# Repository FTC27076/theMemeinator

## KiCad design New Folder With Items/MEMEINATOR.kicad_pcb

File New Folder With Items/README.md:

# theMemeinator

This is my week 3 project. 
This week I designed something kinda like week 1; it's a speaker thingy that reads recording files and plays them.

# Components I used:

4xAA battery holder

USB_C PORT

Potentiometer (for volume)

five push switches (1 for reseting, 1 for ____, 3 for cataloging and choosing )

1 slide switch for power

ESP32 S3 Wroom-1

DFPlayer mini

MCP1825s

# Passive components:

Resistors

capacitors 

Schotty diode

two 2 pin JST PH connector

## FINAL PRODUCT:

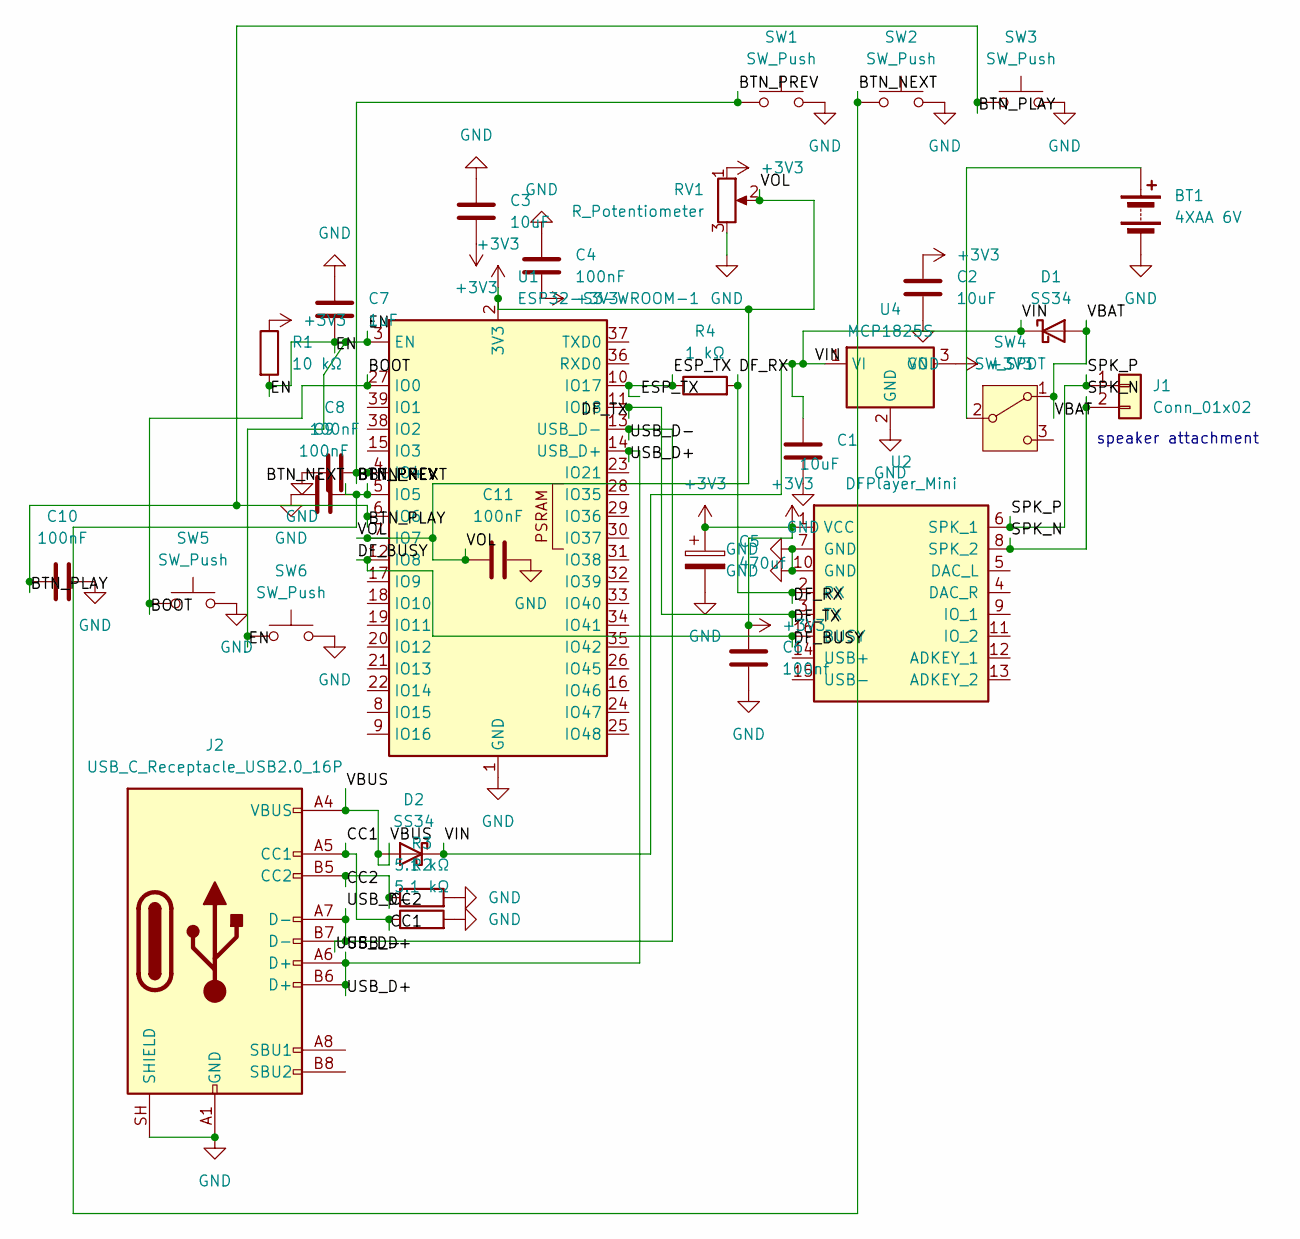
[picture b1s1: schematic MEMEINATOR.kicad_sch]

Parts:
BT1: 4XAA 6V; JST_PH_B2B-PH-K_1x02_P2.00mm_Vertical
C1, C2, C3: 10uF; C_Disc_D3.0mm_W1.6mm_P2.50mm
C4, C8, C9, C10, C11: 100nF; C_Disc_D3.0mm_W1.6mm_P2.50mm
C5: 470uf; CP_Radial_D8.0mm_P3.50mm
C6: 100nf; C_Disc_D3.0mm_W1.6mm_P2.50mm
C7: 1uF; C_Disc_D3.0mm_W1.6mm_P2.50mm
D1, D2: SS34; D_DO-201AD_P15.24mm_Horizontal
J1: Conn_01x02; JST_PH_B2B-PH-K_1x02_P2.00mm_Vertical
J2: USB_C_Receptacle_USB2.0_16P; USB_C_Receptacle_GCT_USB4105-xx-A_16P_TopMnt_Horizontal
R1: 10 kΩ; R_Axial_DIN0204_L3.6mm_D1.6mm_P5.08mm_Horizontal
R2, R3: 5.1 kΩ; R_Axial_DIN0204_L3.6mm_D1.6mm_P5.08mm_Horizontal
R4: 1 kΩ; R_Axial_DIN0204_L3.6mm_D1.6mm_P5.08mm_Horizontal
RV1: R_Potentiometer; Potentiometer_Alps_RK09K_Single_Vertical
SW1, SW2, SW3, SW5, SW6: SW_Push; SW_PUSH_6mm
SW4: SW_SPDT; SW_Slide_SPDT_Angled_CK_OS102011MA1Q
U1: ESP32-S3-WROOM-1; ESP32-S3-WROOM-1ThermalVia0.3
U2: DFPlayer_Mini
U4: MCP1825S; TO-220-3_Horizontal_TabDown

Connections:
+3V3: C2.1, C3.2, C4.2, C5.1, C6.1, C11.1, R1.1, RV1.1, RV1.2, U1.2 (3V3), U1.7 (IO7), U2.1 (VCC), U4.3 (VO)
/BOOT: SW5.1, U1.27 (IO0)
/BTN_NEXT: C9.2, SW2.1, U1.5 (IO5)
/BTN_PLAY: C10.1, SW3.1, U1.6 (IO6)
/BTN_PREV: C8.2, SW1.1, U1.4 (IO4)
/CC1: J2.A5 (CC1), R2.1
/CC2: J2.B5 (CC2), R3.1
/DF_BUSY: U1.12 (IO8), U2.16 (BUSY)
/DF_RX: R4.2, U2.2 (RX)
/DF_TX: U1.11 (IO18), U2.3 (TX)
/EN: C7.2, R1.2, SW6.1, U1.3 (EN)
/ESP_TX: R4.1, U1.10 (IO17)
/SPK_N: J1.2, U2.8 (SPK_2)
/SPK_P: J1.1, U2.6 (SPK_1)
/USB_D+: J2.A6 (D+), J2.B6 (D+), U1.14 (USB_D+)
/USB_D-: J2.A7 (D-), J2.B7 (D-), U1.13 (USB_D-)
/VBAT: D1.2 (A), SW4.1 (A)
/VBUS: D2.2 (A), J2.A4 (VBUS), J2.A9 (VBUS), J2.B4 (VBUS), J2.B9 (VBUS)
/VIN: C1.1, D1.1 (K), D2.1 (K), U4.1 (VI)
GND: BT1.2 (-), C1.2, C2.2, C3.1, C4.1, C5.2, C6.2, C7.1, C8.1, C9.1, C10.2, C11.2, J2.A1 (GND), J2.A12 (GND), J2.B1 (GND), J2.B12 (GND), J2.SH (SHIELD), R2.2, R3.2, RV1.3, SW1.2, SW2.2, SW3.2, SW5.2, SW6.2, U1.1 (GND), U1.40 (GND), U1.41 (GND), U2.7 (GND), U2.10 (GND), U4.2 (GND)
unnamed: BT1.1 (+), SW4.2 (B)

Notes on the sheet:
speaker attachment

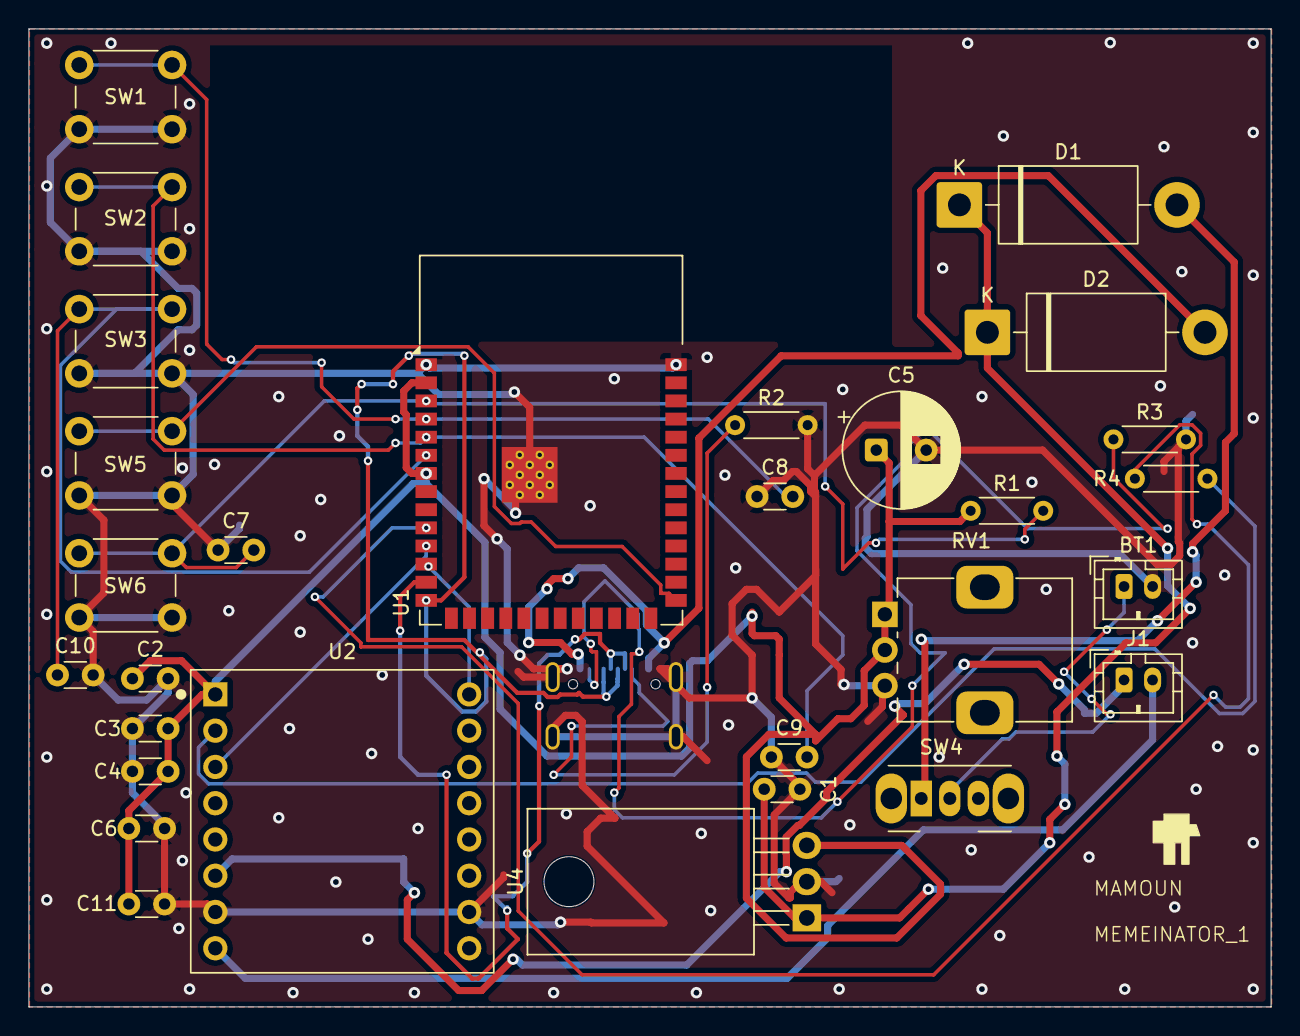
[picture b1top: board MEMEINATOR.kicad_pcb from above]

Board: 2 copper layers, 87.0 x 68.5 mm, 30 parts (1 on the bottom side), 21 nets.

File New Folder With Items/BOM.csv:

"Reference","Qty","Value","DNP","Exclude from BOM","Exclude from Board","Exclude from Simulation","Exclude from Position Files","Footprint","Datasheet"
"U4","1","MCP1825S","","","","","${EXCLUDE_FROM_POS_FILES}","Package_TO_SOT_THT:TO-220-3_Horizontal_TabDown","http://ww1.microchip.com/downloads/en/devicedoc/22056b.pdf"
"U2","1","DFPlayer_Mini","","","","","${EXCLUDE_FROM_POS_FILES}","DFPLAYer:DFPlayer_Mini","https://wiki.dfrobot.com/DFPlayer_Mini_SKU_DFR0299"
"U1","1","ESP32-S3-WROOM-1","","","","","${EXCLUDE_FROM_POS_FILES}","RF_Module:ESP32-S3-WROOM-1ThermalVia0.3","https://www.espressif.com/sites/default/files/documentation/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"
"SW4","1","SW_SPDT","","","","","${EXCLUDE_FROM_POS_FILES}","Button_Switch_THT:SW_Slide_SPDT_Angled_CK_OS102011MA1Q",""
"SW1,SW2,SW3,SW5,SW6","5","SW_Push","","","","","${EXCLUDE_FROM_POS_FILES}","Button_Switch_THT:SW_PUSH_6mm",""
"RV1","1","R_Potentiometer","","","","","${EXCLUDE_FROM_POS_FILES}","Potentiometer_THT:Potentiometer_Alps_RK09K_Single_Vertical",""
"R4","1","1 kΩ","","","","","${EXCLUDE_FROM_POS_FILES}","Resistor_THT:R_Axial_DIN0204_L3.6mm_D1.6mm_P5.08mm_Horizontal",""
"R2,R3","2","5.1 kΩ","","","","","${EXCLUDE_FROM_POS_FILES}","Resistor_THT:R_Axial_DIN0204_L3.6mm_D1.6mm_P5.08mm_Horizontal",""
"R1","1","10 kΩ","","","","","${EXCLUDE_FROM_POS_FILES}","Resistor_THT:R_Axial_DIN0204_L3.6mm_D1.6mm_P5.08mm_Horizontal",""
"J2","1","USB_C_Receptacle_USB2.0_16P","","","","","${EXCLUDE_FROM_POS_FILES}","Connector_USB:USB_C_Receptacle_GCT_USB4105-xx-A_16P_TopMnt_Horizontal","https://www.usb.org/sites/default/files/documents/usb_type-c.zip"
"J1","1","Conn_01x02","","","","","${EXCLUDE_FROM_POS_FILES}","Connector_JST:JST_PH_B2B-PH-K_1x02_P2.00mm_Vertical",""
"D1,D2","2","SS34","","","","","${EXCLUDE_FROM_POS_FILES}","Diode_THT:D_DO-201AD_P15.24mm_Horizontal","https://www.vishay.com/docs/88751/ss32.pdf"
"C7","1","1uF","","","","","${EXCLUDE_FROM_POS_FILES}","Capacitor_THT:C_Disc_D3.0mm_W1.6mm_P2.50mm",""
"C6","1","100nf","","","","","${EXCLUDE_FROM_POS_FILES}","Capacitor_THT:C_Disc_D3.0mm_W1.6mm_P2.50mm",""
"C5","1","470uf","","","","","${EXCLUDE_FROM_POS_FILES}","Capacitor_THT:CP_Radial_D8.0mm_P3.50mm",""
"C4,C8,C9,C10,C11","5","100nF","","","","","${EXCLUDE_FROM_POS_FILES}","Capacitor_THT:C_Disc_D3.0mm_W1.6mm_P2.50mm",""
"C1,C2,C3","3","10uF","","","","","${EXCLUDE_FROM_POS_FILES}","Capacitor_THT:C_Disc_D3.0mm_W1.6mm_P2.50mm",""
"BT1","1","4XAA 6V","","","","","${EXCLUDE_FROM_POS_FILES}","Connector_JST:JST_PH_B2B-PH-K_1x02_P2.00mm_Vertical",""
